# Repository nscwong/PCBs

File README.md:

PCBs
====

A collection of my PCB work. I use EAGLE. Not all are production-ready.

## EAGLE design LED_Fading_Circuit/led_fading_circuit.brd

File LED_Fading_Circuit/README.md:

LED Fading Circuit
==================

A circuit that fades an LED. Small enough to print cheaply and put in various places, such as in a car or keychain.

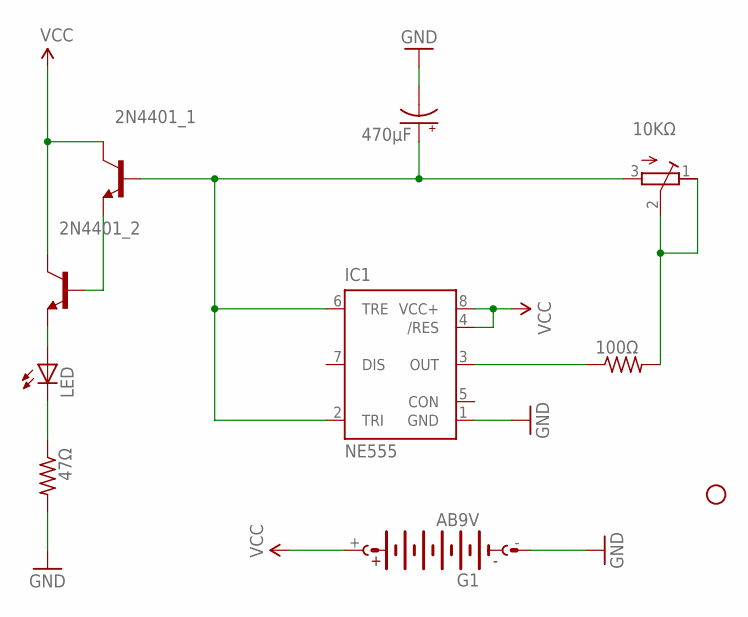
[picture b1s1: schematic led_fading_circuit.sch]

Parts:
2N4401_1, 2N4401_2: -NPN-TO92-EBC; TO92-EBC
10KΩ: R-TRIMMT93XA; RTRIMT93XA
47Ω: R-US_0204/7; 0204/7
100Ω: R-US_0207/10; 0207/10
470µF: CPOL-USE2.5-6; E2,5-6
G1: AB9V
IC1: NE555; DIL-08
LED: LED5MM
STANDOFF1: STAND-OFF

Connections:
GND: 47Ω.2, 470µF.-, G1.-, IC1.1 (GND)
unnamed: 2N4401_1.E, 2N4401_2.B
unnamed: 2N4401_2.E, LED.A
unnamed: 47Ω.1, LED.K (C)
unnamed: 2N4401_1.B, 10KΩ.3 (E), 470µF.+, IC1.2 (TRI), IC1.6 (TRE)
unnamed: 100Ω.1, IC1.3 (OUT)
unnamed: 10KΩ.1 (A), 10KΩ.2 (S), 100Ω.2
VCC: 2N4401_1.C, 2N4401_2.C, G1.+, IC1.4 (/RES), IC1.8 (VCC+)

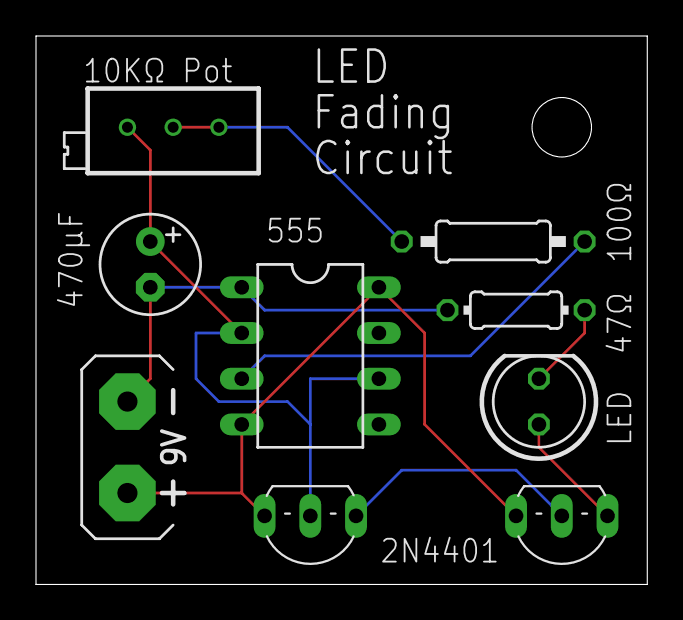
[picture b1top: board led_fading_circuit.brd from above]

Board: 2 copper layers, 34.0 x 30.5 mm, 10 parts (0 on the bottom side), 8 nets.

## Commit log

2014-04-14 Edited README. Added LED Fading Circuit, and current Micromouse.

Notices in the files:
parts and their libraries:
SparkFun-Electromechanical: Licensing: CC v3.0 Share-Alike You are welcome to use this library for commercial purposes.
